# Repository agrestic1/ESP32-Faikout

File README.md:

## Support

You can support this project in many ways, including testing and diagnostics, merge requests, clearly described issues and suggestions, and [buying Faikout boards from us](https://shop.revk.uk?mrlHiG1i). Thank you all for your support. This is open source so others can make and sell (with trademark restrictions). AI based bug reports or MRs will get you blocked.

# ESP32-Faikout

Everyone knows Daikin make some of the best air conditioners out there, mechanically speaking. Sadly their WiFi control modules are not so good, especially the latest models which are all cloud based, require an internet connection to even work, and are slow.

This code/module provides local control via web interface, MQTT, and HomeAssistant integration, all with no cloud crap.

* There is also a new [Faikout Remote Control](https://remote.revk.uk/) available, BLE linked to the Faikout, with environmental sensors, available now.

I'd like to thank the contributors, but contributions are made and accepted on basis that you issue your contribution under the same GPL licence as the project. Forks are allowed on the basis that your forks are on the same GPL licence as the project.

## Trademark

This is an open source project, but bear in mind you cannot sell boards bearing the Andrews & Arnold Ltd name, the A&A logo, the registered trademark Faikout, the registered trademark AJK logo, or the GS1 allocated EANs assigned to Andrews & Arnold Ltd.

Note the name change from Faikin to Faikout as Daikin complained to Amazon and caused a lot of issues. As such Faikout is now a registered trademark to avoid such issues.

## Home Assistant Integration

There has been a lot of work on integrating with Home Assistant as a climate device, and other sensors. This is all based on using MQTT (either HA mosquitto broker, or a broker to which HA also connects). This provides real time responses and sensor data and works very well.

In addition, for other management systems than HA, the *legacy* Daikin local HTTP URLs are also supported to some extent. The support coverage is not as good, and maintence of this is less of a priority - but as always (human) suggestions and pull requests are welcome in this area. If you are using the old Daikin HA integration which uses these legacy HTTP URLs, please update to using MQTT. The config is automatic over MQTT - you just have to set the broken, username, and password. 

## Further manuals / links

- [Work in progress](https://codeberg.org/RevK/ESP32-Faikout/wiki/Work-in-progress)
- [Wiring](https://codeberg.org/RevK/ESP32-Faikout/wiki/Wiring)
- [Setup](Manuals/Setup.md) Manual
- [Controls](Manuals/Controls.md) Manual
- [Advanced](Manuals/Advanced.md) Manual
- [ESP8266 port](https://github.com/Sonic-Amiga/ESP8266-Faikin) of this code
- [list of supported air-con](https://codeberg.org/RevK/ESP32-Faikout/wiki/List-of-confirmed-working-air-con-units) WiKi (please update as needed)
- [DoC](Manuals/DoC.md) and Vulnerability disclosure policy
- [S21](Manuals/S21.md) reverse engineered details of `S21` protocol

For support, see issues.

## Safety

Always propely isolate power before opening your air-con. Take care as dangerous voltages. Some connector types have dangerous voltage in operation.

### Ethernet (and WiFi)

The Ethernet board has an RJ45 10/100 Ethernet connector for improved reliability and privacy. The Ethernet has an isolating transformer and clearances, but I have to stress **this is a prototype/dev board for specialist/hobbyist use only, and is NOT certified for grid power safety isolation. DO NOT USE WITH X403 CONNECTOR or any connector with dangerous voltages.**

### PoE Ethernet (and WiFi)

The PoE Ethernet board has an RJ45 10/100 Ethernet connector for improved reliability and privacy, with PoE power for the Faikout module. The PoE power module has electrical isolation. The board also has opto isolators for the S21 connection, electrically isolating it from the air conditioning unit. This adds extra layers of safety, however I have to stress **this is a prototype/dev board for specialist/hobbyist use only, and is NOT certified for grid power safety isolation.**

*Note that Ethernet uses more power - there are some Daikin models with much less power from the air-con, for these PoE may be a better choice for Ethernet use, as the main board (and Ethernet chip) is powered from the PoE, and not the air-con.*

## PCB and case

Buy from [shop.revk.uk](https://shop.revk.uk?mrlHiG1i). Also available from a third party in Australia eBay.

New Ethernet option.

New Opto-isiolated PoE Ethernet option.

Board are supplied in a panel, with snap off parts. The basic Faikout board can be two sizes 45x36mm or 40x16mm.

## Why I made this

The history is that, after years of using Daikin air-con in my old home, and using the local http control, in my new house in Wales the WiFi was all cloud based with no local control, and useless, and slow. Just configuring it was a nightmare. I spent all day reverse engineering it and making a new module to provide local control. Pull requests and feature ideas welcome.

This whole project is almost entirely by me, but with some valuable contributions from others (thank you). All of my bits are copyright by me and Andrews & Arnold Ltd who sponsor the whole project, and released under GPL. Whilst not required by the licence, attribution and links would be appreciated if you reuse this.

## How to get one

But also, the PCB designs are published, including production files for [JLCPCB](https://jlcpcb.com). You need to remove trademarks, etc, and you would also need something to program them (TC2030 lead). Obviously you need some experience with PCB ordering and diagnostics if getting your own boards made.

# Set-up

Appears as access point with simple web page to set up on local WiFI. On iPhone the setup page auto-loads.

# Operation

Local interactive web control page using *hostname*.local, no app required, no external internet required.

- [Setup](Manuals/Setup.md) Manual
- [Controls](Manuals/Controls.md) Manual
- [Advanced](Manuals/Advanced.md) Manual

# Design

* KiCad PCB designs included, with JLCPCB production files
* 3D printed case STL files
* Documentation of reverse engineered protocol included

Basically, Daikin have gone all cloudy with the latest WiFi controllers. This module is designed to provide an alternative.

* Simple local web based control with live websocket status, easy to save as desktop icon on a mobile phone
* MQTT reporting and controls
* Works with Home Assistant over MQTT - note Home Assistant can work with HomeKit
* Includes linux mysql/mariadb based logging and graphing tools
* Works with [EnvMon](https://codeberg.org/RevK/ESP32-EnvMon) Environmental Monitor for finer control and status display
* or, works with BlueCoinT and Telink [BLE temperature sensor](Manuals/BLE.md) as a remote reference in an auto mode
* Automatically works out if S21 or X50 protocol (used on bigger/ducted units)
* Backwards compatible direct `/aircon/...` URLs

# Building code yourself

Git clone this `--recursive` to get all the submodules, and it should build with just `make`. There are make targets for other variations, but this hardware is the `make pico` or `make s3` version. The `make` actually runs the normal `idf.py` to build which then uses cmake. `make menuconfig` can be used to fine tune the settings, but the defaults should be mostly sane. `make flash` should work to program. If flashing yourself, you will need a programming lead, e.g. [Tazmotizer](https://codeberg.org/RevK/Tasmotizer-PCB) or similar, and of course the full ESP IDF environment. The latest boards also have 4 pads for direct USB connection to flash with no adaptor. The modules on Amazon come pre-loaded and can upgrade over the air.

The code is normally set up to automatically upgrade the software, checking roughly once a week. You can change this in settings via MQTT.

If you build yourself, you either need no code signing, or your own signing key. This will break auto-updates which try to load my code releases, so you need to adjuist settings `otahost` and `otaauto` accordingly. You can set these in the build config, along with WiFi settings, etc.

## Flashing code

You will need to connect a suitable programming lead. Boards have a tag-connect compatible header for a [TC2030-USB-NL](https://www.tag-connect.com/product/tc2030-usb-nl) lead. Note that the latest boards have test pads on the back which include USB, so you can solder a USB lead if necessary.

See [https://codeberg.org/RevK/ESP32-RevK](https://codeberg.org/RevK/ESP32-RevK) for more details of how to flash the files easily.

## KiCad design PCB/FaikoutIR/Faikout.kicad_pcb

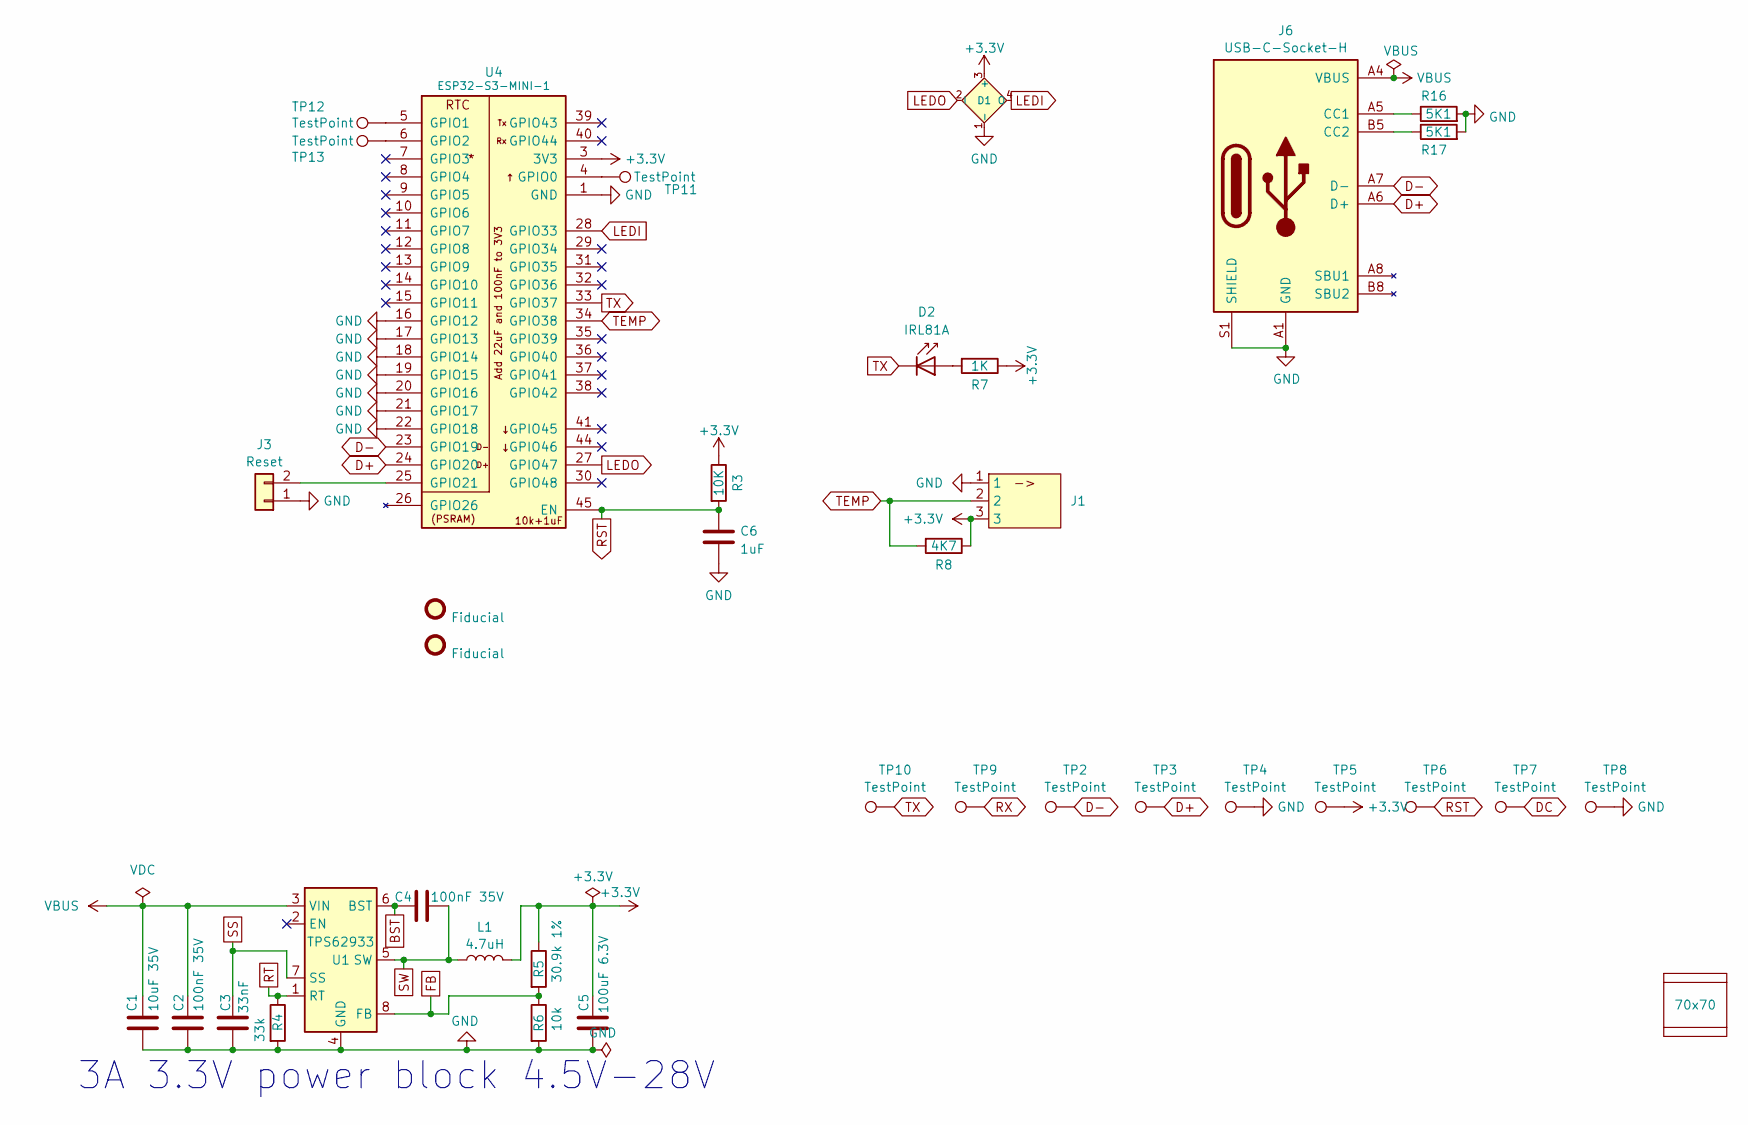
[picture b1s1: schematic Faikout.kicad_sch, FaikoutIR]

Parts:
C1: 10uF 35V; C_0603; MPN C22367827
C2, C4: 100nF 35V; C_0201; MPN C181043
C3: 33nF; C_0201; MPN C5142554
C5: 100uF 6.3V; C_0805; MPN C141660
C6: 1uF; C_0201
D1: XL-1615RGBC-2812B; SMD1615; MPN C5349954
D2: IRL81A; LED_SideEmitter_Rectangular_W4.5mm_H1.6mm
FID2, FID3: Fiducial; Fiducial_1mm_Mask2mm
J1: Wago; WAGO-2060-453-998-404; MPN C2765056
J3: Reset; AA-Pad
J6: USB-C-Socket-H; MPN C709357
L1: 4.7uH; L_6x6; MPN C32684
PCB1: 70x70; PCB7070
R3: 10K; R_0201; MPN C106225
R4: 33k; R_0201; MPN C473534
R5: 30.9k 1%; R_0201; MPN C473585
R6: 10k; R_0201; MPN C106225
R7: 1K; R_0201
R8: 4K7; R_0201
R16, R17: 5K1; R_0201; MPN C473460
TP2, TP3, TP4, TP5, TP6, TP7, TP8, TP9, TP10, TP11, TP12, TP13: TestPoint; PAD-2mm
U1: TPS62933; SOT-583-8; MPN C3200405
U4: ESP32-S3-MINI-1; MPN C3013941
V3, V4: VCUT70N

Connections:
+3.3V: C5.1, D1.3 (+), J1.3, L1.2, R3.1, R5.1, R7.1, R8.1, TP5.1 (1_1), U4.3 (3V3)
BST: C4.1, U1.6 (BST)
D+: J6.A6 (D+), J6.B6 (D+), TP3.1 (1_1), U4.24 (GPIO20)
D-: J6.A7 (D-), J6.B7 (D-), TP2.1 (1_1), U4.23 (GPIO19)
DC: TP7.1 (1_1)
FB: R5.2, R6.1, U1.8 (FB)
GND: C1.2, C2.2, C3.2, C5.2, C6.2, D1.1 (-), J1.1, J3.1, J6.A1 (GND), J6.A12 (GND), J6.B1 (GND), J6.B12 (GND), J6.S1 (SHIELD), R4.2, R6.2, R16.2, R17.2, TP4.1 (1_1), TP8.1 (1_1), U1.4 (GND), U4.1 (GND), U4.2 (GND), U4.16 (GPIO12), U4.17 (GPIO13), U4.18 (GPIO14), U4.19 (GPIO15), U4.20 (GPIO16), U4.21 (GPIO17), U4.22 (GPIO18), U4.42 (GND), U4.43 (GND), U4.46 (GND), U4.47 (GND), U4.48 (GND), U4.49 (GND), U4.50 (GND), U4.51 (GND), U4.52 (GND), U4.53 (GND), U4.54 (GND), U4.55 (GND), U4.56 (GND), U4.57 (GND), U4.58 (GND), U4.59 (GND), U4.60 (GND), U4.61 (GND), U4.62 (GND), U4.63 (GND), U4.64 (GND), U4.65 (GND)
LEDI: D1.4 (O), U4.28 (GPIO33)
LEDO: D1.2 (I), U4.27 (GPIO47)
unnamed: D2.2 (A), R7.2
unnamed: J3.2, U4.25 (GPIO21)
unnamed: J6.A5 (CC1), R16.1
unnamed: J6.B5 (CC2), R17.1
unnamed: TP11.1 (1_1), U4.4 (GPIO0)
unnamed: TP12.1 (1_1), U4.5 (GPIO1)
unnamed: TP13.1 (1_1), U4.6 (GPIO2)
RST: C6.1, R3.2, TP6.1 (1_1), U4.45 (EN)
RT: R4.1, U1.1 (RT)
RX: TP9.1 (1_1)
SS: C3.1, U1.7 (SS)
SW: C4.2, L1.1, U1.5 (SW)
TEMP: J1.2, R8.2, U4.34 (GPIO38)
TX: D2.1 (K), TP10.1 (1_1), U4.33 (GPIO37)
VBUS: C1.1, C2.1, J6.A4 (VBUS), J6.A9 (VBUS), J6.B4 (VBUS), J6.B9 (VBUS), U1.3 (VIN)

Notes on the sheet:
3A 3.3V power block 4.5V-28V

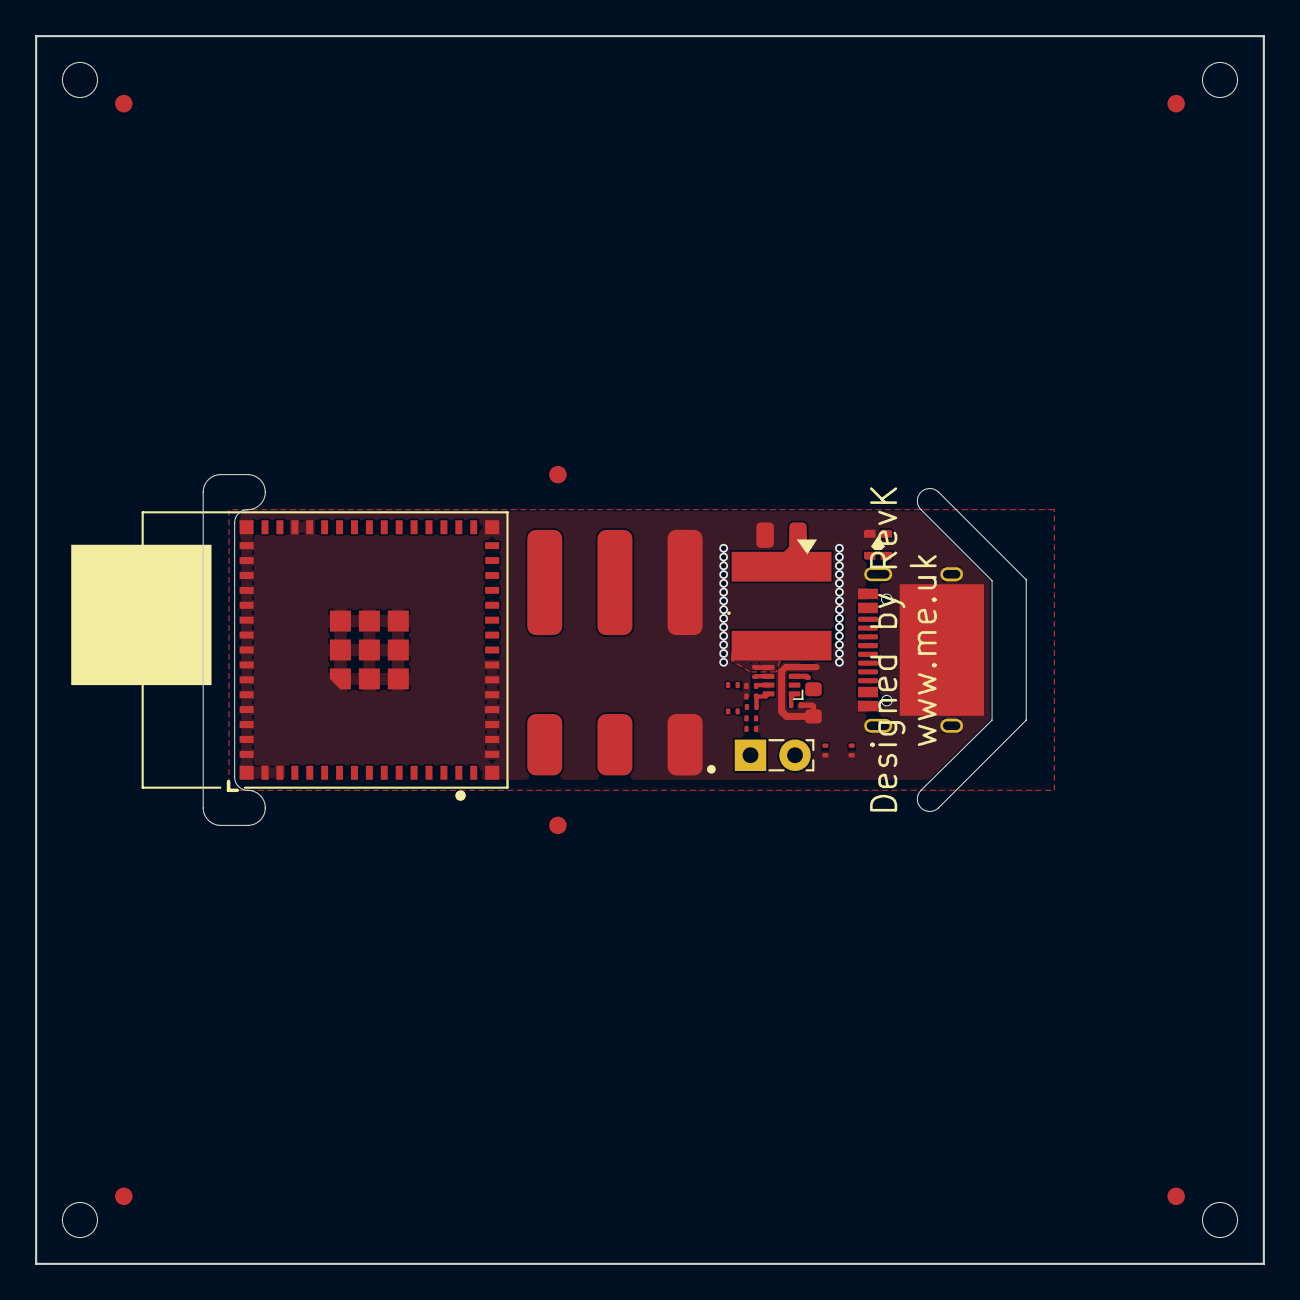
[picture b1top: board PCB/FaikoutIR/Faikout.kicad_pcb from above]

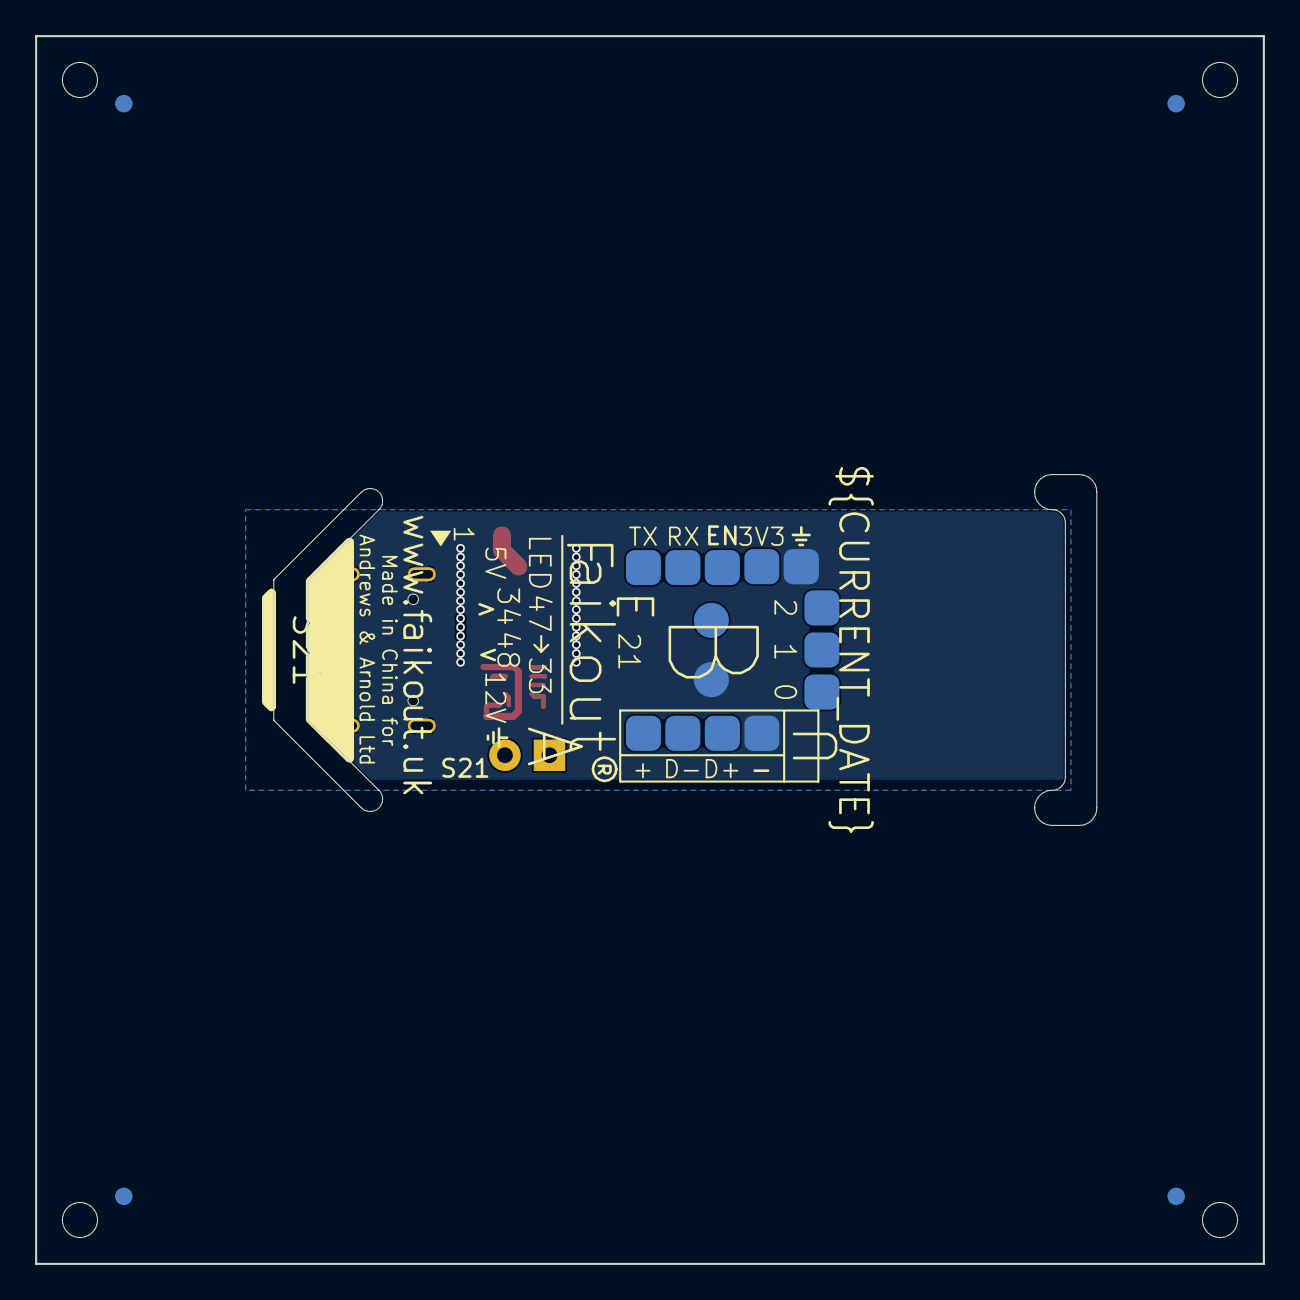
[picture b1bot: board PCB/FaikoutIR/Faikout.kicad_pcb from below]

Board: 2 copper layers, 70.0 x 70.0 mm, 39 parts (13 on the bottom side), 22 nets.

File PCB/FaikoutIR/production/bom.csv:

Designator,Footprint,Quantity,Value,LCSC Part #
C1,C_0603,1,10uF 35V,C22367827
"C2, C4",C_0201,2,100nF 35V,C181043
C3,C_0201,1,33nF,C5142554
C5,C_0805,1,100uF 6.3V,C141660
C6,C_0201,1,1uF,
D1,SMD1615,1,XL-1615RGBC-2812B,C5349954
D2,LED_SideEmitter_Rectangular_W4.5mm_H1.6mm,1,IRL81A,
J1,WAGO-2060-453-998-404,1,Wago,C2765056
J6,USB-C-Socket-H,1,USB-C-Socket-H,C709357
L1,L_6x6,1,4.7uH,C32684
"R16, R17",R_0201,2,5K1,C473460
"R3, R6",R_0201,2,10K,C106225
R4,R_0201,1,33k,C473534
R5,R_0201,1,30.9k 1%,C473585
R7,R_0201,1,1K,
R8,R_0201,1,4K7,
U1,SOT-583-8,1,TPS62933,C3200405
U4,ESP32-S3-MINI-1,1,ESP32-S3-MINI-1,C3013941

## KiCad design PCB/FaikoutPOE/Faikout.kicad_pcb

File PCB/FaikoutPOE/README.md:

# FaikoutPOE

## Trademark

This project is subject to the licence in the LICENCE file, and even if that says it is an open source project, you cannot sell boards or cases bearing the Andrews & Arnold Ltd name, the A&A logo, the registered trademark AJK logo, or other registered trademarks, or any GS1 allocated EANs/barcode assigned to Andrews & Arnold Ltd.

## PCB Designs

These files are for use with [KiCAD](https://www.kicad.org).

- [Faikout](Faikout.kicad_pro)

## 3D

3D case designs are normally automatically created from the PCB so as to ensure correct details and placement of apertures, etc.

|Design|Bottom|Top|Combined|
|------|------|---|--------|
|Faikout||||

## PCB Images Faikout

---

*Auto generated README.md 2026-10-20T12:44:44*

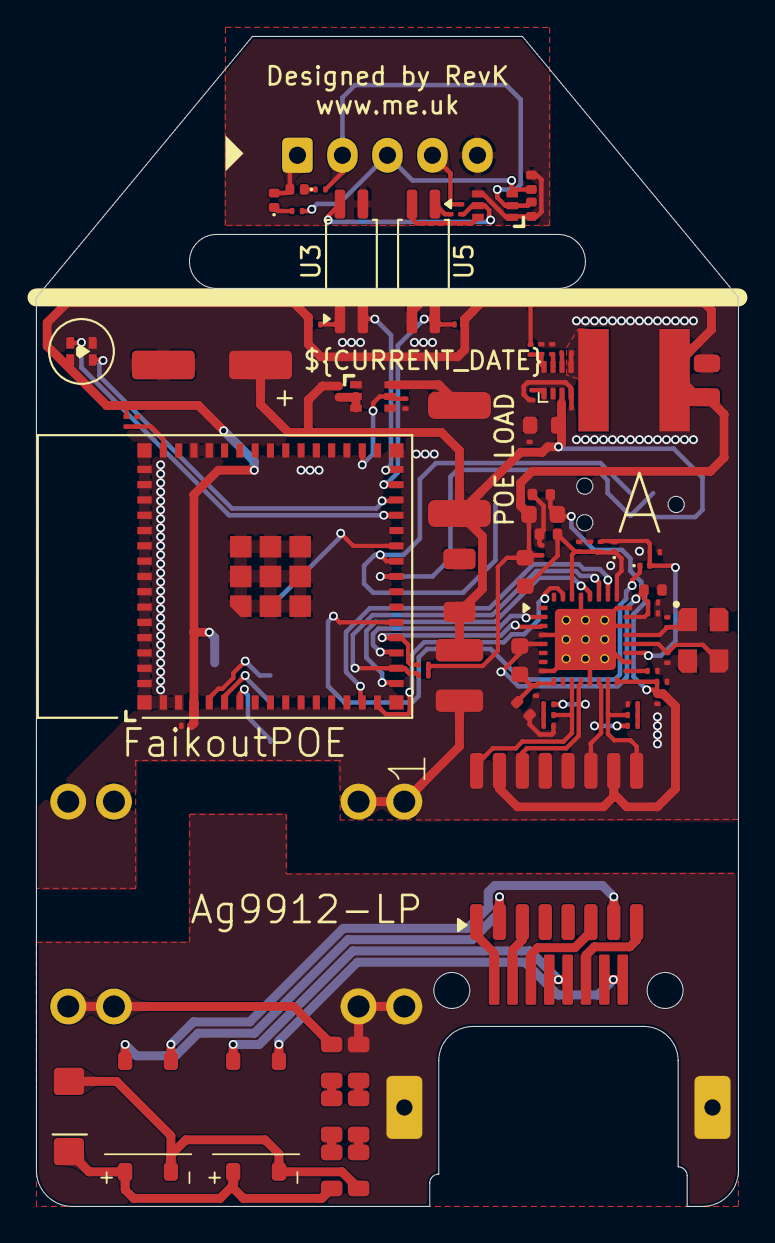
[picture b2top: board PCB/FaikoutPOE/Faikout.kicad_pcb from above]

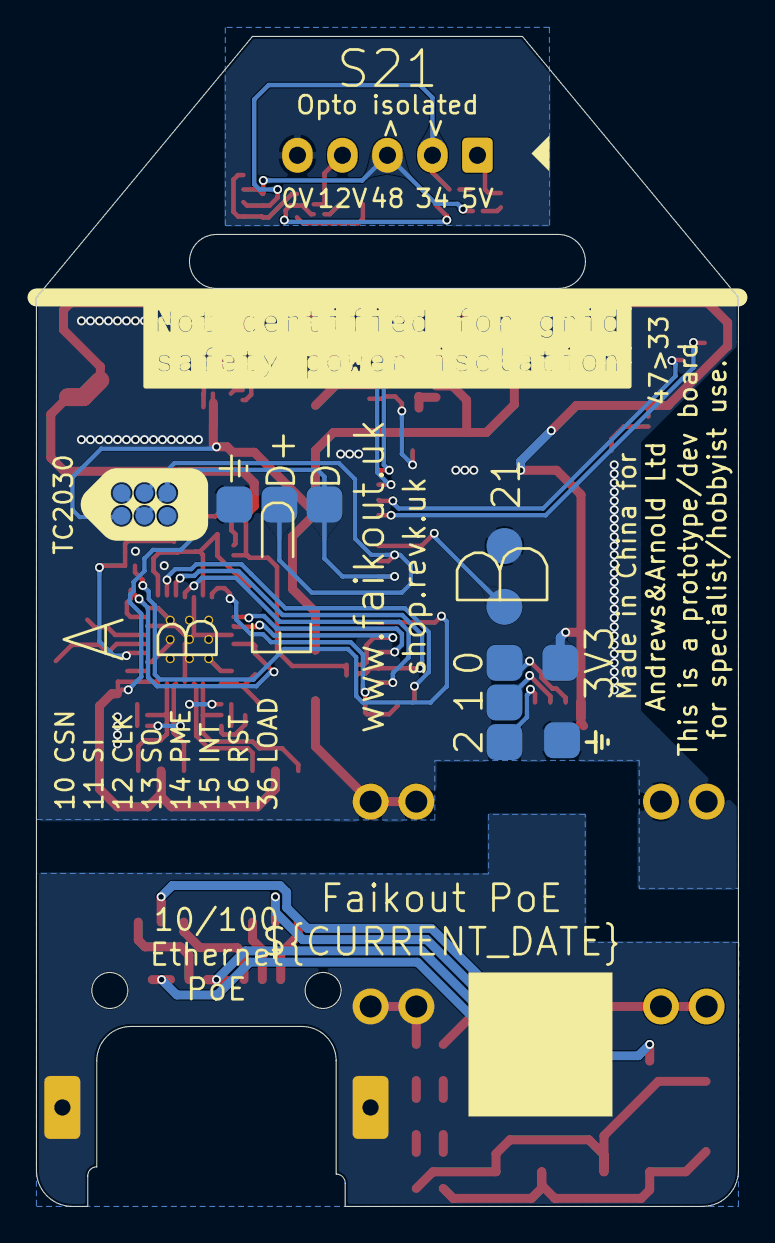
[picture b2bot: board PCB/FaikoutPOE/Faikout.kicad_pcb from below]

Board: 2 copper layers, 39.0 x 65.0 mm, 91 parts (10 on the bottom side), 71 nets.

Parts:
C1, C3, C4, C6, C8, C9, C11, C12, C13, C17, C34: 100nF; C_0201
C2, C5, C7, C10: 22uF; C_0402
C14, C15: 20pF; C_0201
C16: 10pF; C_0201
C18: 10uF 35V; C_0603
C19, C21, C22: 100nF 35V; C_0201
C20: 33nF; C_0201
C23: 100uF 6.3V; C_0805
C25: 10uF 50V; C_1206
C26: 100uF 50V; CP_Elec_6.3x7.7
C36: 1uF; C_0201
D1, D2: BAT30F4; D_0201
D4: XL-1615RGBC-2812B; SMD1615-Side
D5, D10: D; D_0402
D6: SMAJ58A; D_SMA
D7, D11: DFN1006-2L
D8, D9: MB4S; TO-269AA-BR
F4: 1210L150/33WR; Fuse_1210
FB3, FB4, FB5: FerriteBead; L_0603
J1: RJ45_LED; RC01516
J3: S21; JST_EH_S5B-EH_1x05_P2.50mm_Horizontal
J5: Reset; AA-Pad
J7: TC2030-USB-NL-DS; Tag-Connect_TC2030-IDC-NL_2x03_P1.27mm_Vertical
L1: 4.7uH; L_6x6
L14, L15, L16, L17, L18, L19: CBG201209U121T; L_0805
M1: Ag9912-LP; Ag9900-LP
P1, P2, P3, P4, P5, P6, P7, P8: Square; PAD-2mm
Q1, Q2: BSS138PS; SOT-363_SC-70-6
R1, R2, R3, R4, R5: 49R9; R_0201
R6, R7, R13, R16, R21, R22, R24: 10k; R_0201
R8: 3k01 1%; R_0201
R9: 10K; R_0201
R10, R17: 1k; R_0201
R11: 33k; R_0201
R18, R19: 4k7; R_0201
R20: 200 1W; R_2512
R23: 30.9k 1%; R_0201
TR1: B1601S
U1: KSZ8851SNL; QFN-32-1EP_5x5mm_P0.5mm_EP3.7x3.7mm-hot
U2: ESP32-S3-MINI-1
U3, U5: TCMT1100; SOP-4_4.4x2.6mm_P1.27mm
U6: TPS62933; SOT-583-8
Y1: Crystal_GND24; Crystal-3.2x2.5

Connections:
+1V8: C8.1, C9.1, C10.1, FB3.1, U1.5 (VDDCO1V8), U1.23 (VDDD1V8)
+3.3V: C17.2, C23.1, C34.2, D4.3 (+), FB4.2, FB5.2, L1.2, P7.1 (P_1), R5.1, R9.1, R17.1, R18.2, R19.2, R23.1, U2.3 (3V3)
BST: C21.1, U6.6 (BST)
CSN: U1.26 (CSN), U2.14 (GPIO10)
D+: J7.4 (D+), P3.1 (P_1), U2.24 (GPIO20)
D-: J7.2 (NC), J7.3 (D-), J7.6 (NC), P2.1 (P_1), U2.23 (GPIO19)
E12: D9.2, TR1.2 (C_TD)
E36: D9.1, TR1.7 (C_RD)
E45: D8.2, J1.4, J1.5
E78: D8.1, J1.7, J1.8
ETHRST: D1.1 (K), U2.20 (GPIO16)
FB: R23.2, R24.1, U6.8 (FB)
GND: C1.2, C2.2, C3.2, C4.2, C5.2, C6.2, C7.2, C8.2, C9.2, C10.2, C11.2, C12.2, C13.2, C14.2, C15.2, C16.2, C17.1, C18.2, C19.2, C20.2, C22.2, C23.2, C25.1, C26.2, C34.1, C36.2, D4.1 (-), J5.1, J7.5 (GND), M1.3 (-VDC), P4.1 (P_1), P8.1 (P_1), Q1.1 (SN), Q1.4 (DP), R8.1, R11.2, R22.2, R24.2, U1.4 (DGND), U1.8 (AGND), U1.13 (AGND), U1.18 (AGND), U1.22 (DGND), U1.24 (DGND), U1.29 (DGND), U1.33 (GND), U2.1 (GND), U2.2 (GND), U2.42 (GND), U2.43 (GND), U2.46 (GND), U2.47 (GND), U2.48 (GND), U2.49 (GND), U2.50 (GND), U2.51 (GND), U2.52 (GND), U2.53 (GND), U2.54 (GND), U2.55 (GND), U2.56 (GND), U2.57 (GND), U2.58 (GND), U2.59 (GND), U2.60 (GND), U2.61 (GND), U2.62 (GND), U2.63 (GND), U2.64 (GND), U2.65 (GND), U5.3, U6.4 (GND), Y1.2 (G), Y1.4 (G)
INTR: R18.1, U1.3 (INTR), U2.19 (GPIO15)
LEDI: D4.4 (O), U2.28 (GPIO33)
LEDO: D4.2 (I), U2.27 (GPIO47)
unnamed: C12.1, R1.1, R2.1
unnamed: C13.1, R3.1, R4.1
unnamed: D5.1 (K), R16.1
unnamed: D6.1 (A1), D8.3 (+), D9.3 (+), L14.1
unnamed: D6.2 (A2), D8.4 (-), D9.4 (-), L15.1
unnamed: D5.2 (A), D10.2 (A), J3.1
unnamed: D10.1 (K), R13.1
unnamed: D11.1, J3.2, Q2.2 (GN), R16.2
unnamed: D7.2, J3.3, Q2.3 (SP), R13.2
unnamed: J5.2, U2.25 (GPIO21)
unnamed: L14.2, L16.1
unnamed: L15.2, L17.1
unnamed: L16.2, L18.1
unnamed: L17.2, L19.1
unnamed: P1.1 (P_1), U2.4 (GPIO0)
unnamed: P5.1 (P_1), U2.5 (GPIO1)
unnamed: P6.1 (P_1), U2.6 (GPIO2)
unnamed: Q1.6 (DN), R20.1
unnamed: Q1.2 (GN), Q1.3 (SP), R21.2
unnamed: Q2.6 (DN), U5.2
unnamed: Q2.5 (GP), R6.2, U3.4
unnamed: R5.2, U3.1
unnamed: R10.2, U5.1
unnamed: J1.3, TR1.6 (RD+)
unnamed: J1.6, TR1.8 (RD-)
unnamed: J1.1, TR1.1 (TD+)
unnamed: J1.2, TR1.3 (TD-)
unnamed: R8.2, U1.17 (ISET)
unnamed: C6.1, C7.1, FB3.2, U1.9 (VDDA1V8)
unnamed: C15.1, U1.20 (X1), Y1.3
unnamed: C14.1, U1.21 (X2), Y1.1
unnamed: C36.1, R9.2, U2.45 (EN)
PME: U1.2 (PME), U2.18 (GPIO14)
POE: F4.2, M1.1 (+VDC), M1.2 (+VDC)
POELOAD: Q1.5 (GP), R22.1, U2.32 (GPIO36)
RSTN: C16.1, D1.2 (A), D2.2 (A), R7.2, U1.19 (RSTN)
RT: R11.1, U6.1 (RT)
RX: R17.2, U2.29 (GPIO34), U5.4
RXN: R1.2, TR1.14 (TX-), U1.12 (RXN)
RXP: R2.2, TR1.16 (TX+), U1.11 (RXP)
S21DC: J3.4, R6.1, R10.1
S21GND: D7.1, D11.2, J3.5, Q2.1 (SN), Q2.4 (DP), U3.3
SCLK: U1.28 (SCLK), U2.16 (GPIO12)
SI: U1.31 (SI), U2.15 (GPIO11)
SO: R19.1, U1.27 (SO), U2.17 (GPIO13)
SS: C20.1, U6.7 (SS)
SW: C21.2, L1.1, U6.5 (SW)
TX: U2.30 (GPIO48), U3.2
TXN: R3.2, TR1.9 (RX-), U1.15 (TXN)
TXP: R4.2, TR1.11 (RX+), U1.14 (TXP)
VDC: C18.1, C19.1, C22.1, C25.2, C26.1, F4.1, J7.1 (VBUS), R20.2, R21.1, U6.3 (VIN)
VDDA3V3: C1.1, C2.1, C11.1, FB4.1, TR1.10 (C_RX), TR1.15 (C_TX), U1.16 (VDDA3V3)
VDDIO: C3.1, C4.1, C5.1, D2.1 (K), FB5.1, R7.1, U1.25 (VDDIO), U1.30 (VDDIO)
VIN+: L18.2, M1.5 (VIN+), M1.6 (VIN+)
VIN-: J1.S, L19.2, M1.7 (VIN-), M1.8 (VIN-)

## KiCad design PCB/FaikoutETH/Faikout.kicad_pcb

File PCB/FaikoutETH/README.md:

# FaikoutETH

## Trademark

This project is subject to the licence in the LICENCE file, and even if that says it is an open source project, you cannot sell boards or cases bearing the Andrews & Arnold Ltd name, the A&A logo, the registered trademark AJK logo, or other registered trademarks, or any GS1 allocated EANs/barcode assigned to Andrews & Arnold Ltd.

## PCB Designs

These files are for use with [KiCAD](https://www.kicad.org).

- [Faikout](Faikout.kicad_pro)

## 3D

3D case designs are normally automatically created from the PCB so as to ensure correct details and placement of apertures, etc.

|Design|Bottom|Top|Combined|
|------|------|---|--------|
|Faikout||||

## PCB Images Faikout

---

*Auto generated README.md 2026-10-20T12:44:34*

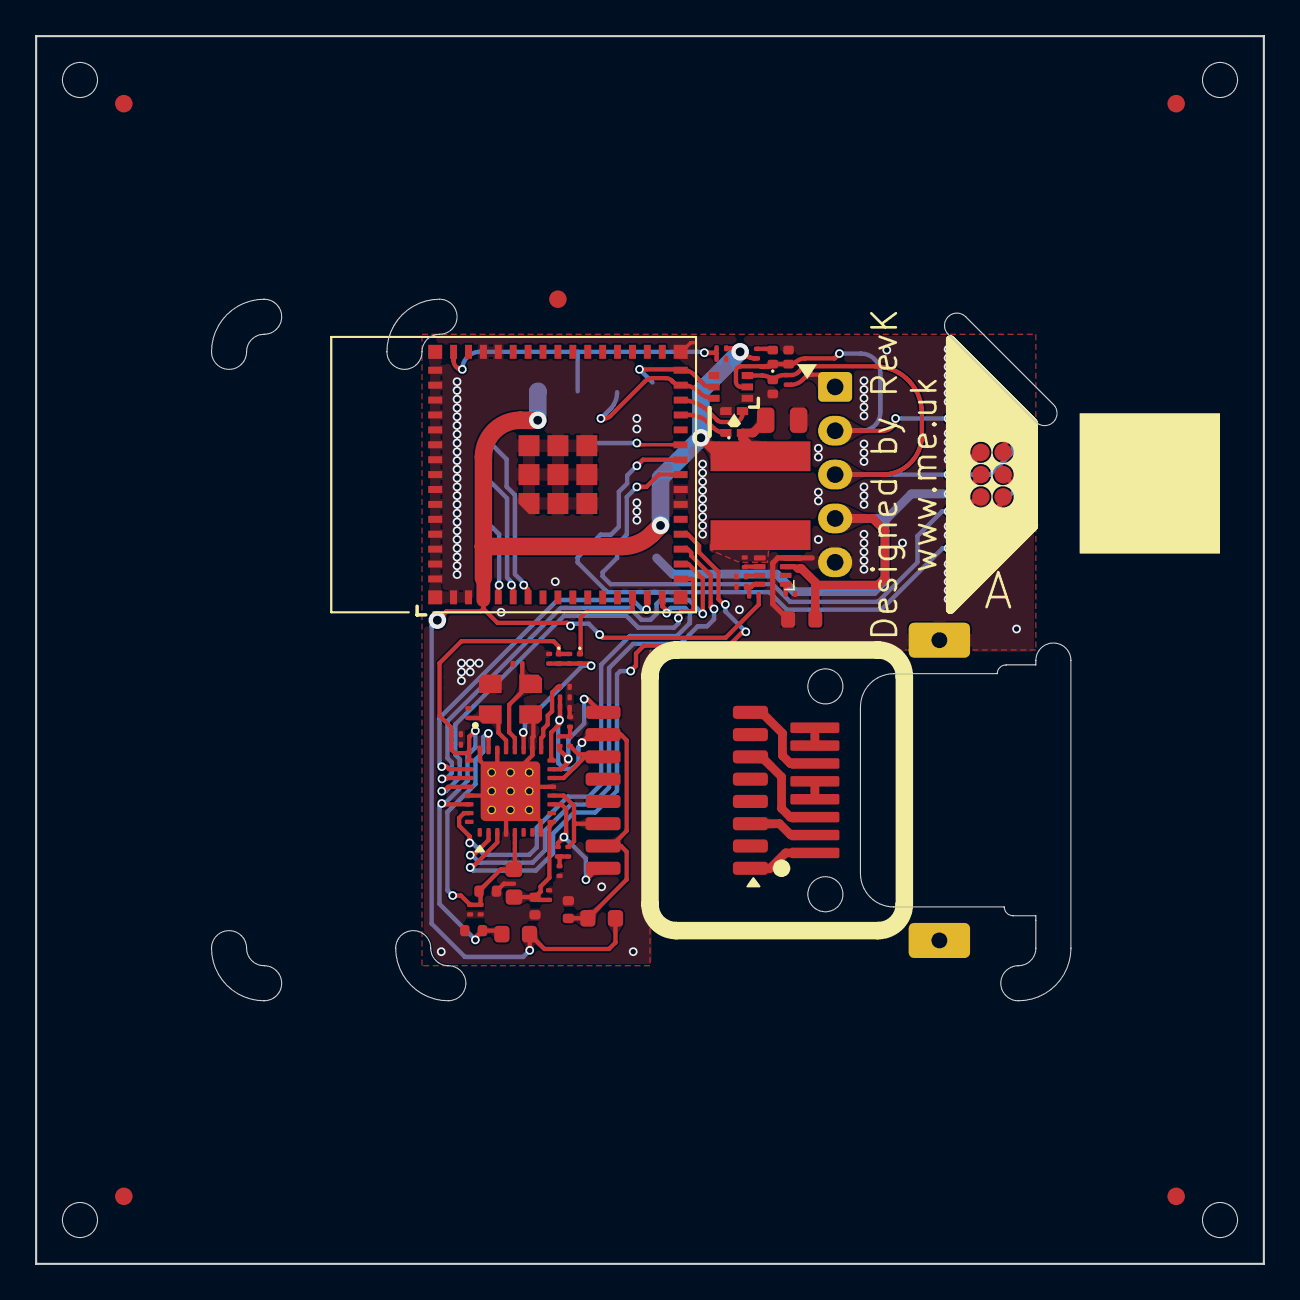
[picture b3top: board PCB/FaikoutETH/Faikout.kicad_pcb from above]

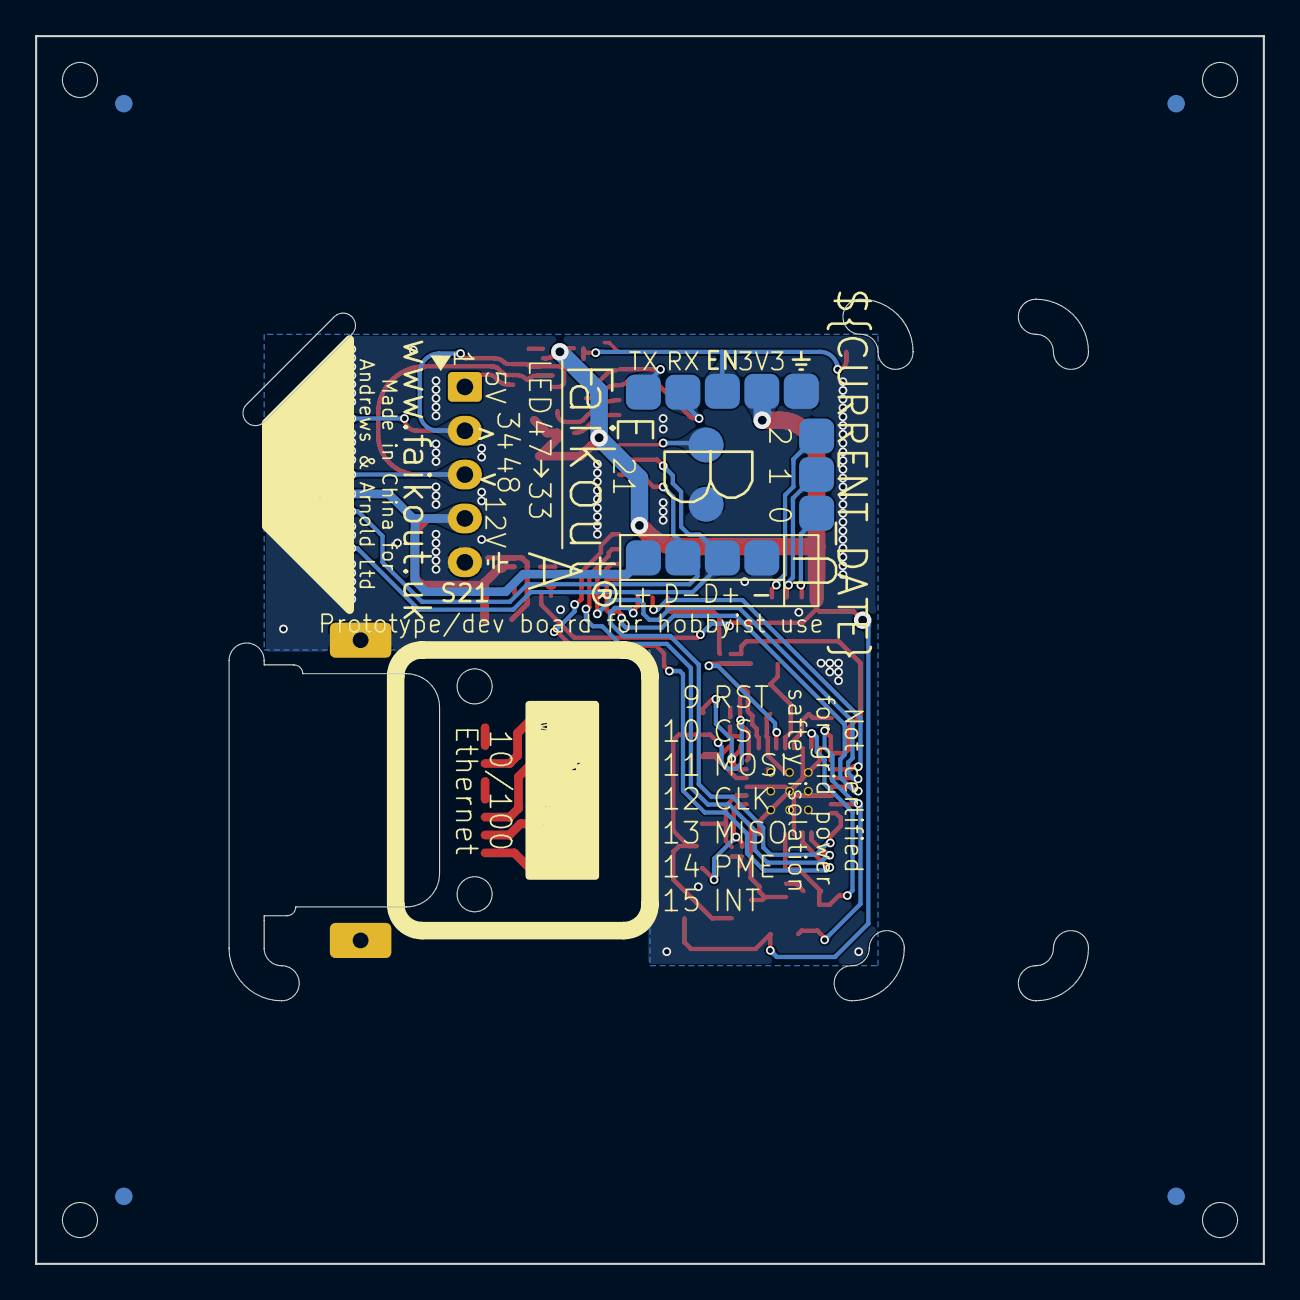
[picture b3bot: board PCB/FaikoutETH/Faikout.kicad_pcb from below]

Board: 2 copper layers, 70.0 x 70.0 mm, 73 parts (14 on the bottom side), 50 nets.

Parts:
C1: 10uF 35V; C_0603
C2, C4: 100nF 35V; C_0201
C3: 33nF; C_0201
C5: 100uF 6.3V; C_0805
C6: 1uF; C_0201
C8, C9, C11, C13, C14, C21, C22, C24, C28: 100nF; C_0201
C10, C12, C23, C25: 22uF; C_0402
C20: 10pF; C_0201
C26, C27: 20pF; C_0201
D1: XL-1615RGBC-2812B; SMD1615
D2, D3: DFN1006-2L
D4: D; D_0402
D5, D6: BAT30F4; D_0201
FB3, FB4, FB5: FerriteBead; L_0603
FID2: Fiducial; Fiducial_1mm_Mask2mm
J1: 1x5; JST_EH_S5B-EH_1x05_P2.50mm_Horizontal
J2: TC2030-USB-NL; Tag-Connect_TC2030-IDC-NL_2x03_P1.27mm_Vertical
J3: Reset; AA-Pad
J4: RJ45_LED; RC01516
L1: 4.7uH; L_6x6
PCB1: 70x70; PCB7070
Q1: BSS138PS; SOT-363_SC-70-6
R1, R2, R7, R8: 10k; R_0201
R3: 10K; R_0201
R4, R9, R10, R11: 49R9; R_0201
R5: 33k; R_0201
R6: 30.9k 1%; R_0201
R12: 3k01 1%; R_0201
TP2, TP3, TP4, TP5, TP6, TP7, TP8, TP9, TP10, TP11, TP12, TP13: TestPoint; PAD-2mm
TR1: B1601S
U1: KSZ8851SNL; QFN-32-1EP_5x5mm_P0.5mm_EP3.7x3.7mm-hot
U2: TPS62933; SOT-583-8
U4: ESP32-S3-MINI-1
V3, V4, V5, V6, V7: VCUT70N
Y1: Crystal_GND24; Crystal-3.2x2.5

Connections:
+1V8: C8.1, C9.1, C10.1, FB3.1, U1.5 (VDDCO1V8), U1.23 (VDDD1V8)
+3.3V: C5.1, D1.3 (+), FB4.2, FB5.2, L1.2, R2.1, R3.1, R6.1, TP5.1 (1_1), U4.3 (3V3)
BST: C4.1, U2.6 (BST)
CSN: U1.26 (CSN), U4.14 (GPIO10)
D+: J2.4 (D+), TP3.1 (1_1), U4.24 (GPIO20)
D-: J2.3 (D-), TP2.1 (1_1), U4.23 (GPIO19)
DC: C1.1, C2.1, J1.4, J2.1 (VBUS), TP7.1 (1_1), U2.3 (VIN)
ETHRST: D5.1 (K), U4.13 (GPIO9)
FB: R6.2, R8.1, U2.8 (FB)
GND: C1.2, C2.2, C3.2, C5.2, C6.2, C8.2, C9.2, C10.2, C11.2, C12.2, C13.2, C14.2, C20.2, C21.2, C22.2, C23.2, C24.2, C25.2, C26.2, C27.2, C28.2, D1.1 (-), D2.1, D3.1, J1.5, J2.5 (GND), J3.1, J4.S, Q1.1 (SN), Q1.4 (DP), R5.2, R8.2, R12.1, TP4.1 (1_1), TP8.1 (1_1), U1.4 (DGND), U1.8 (AGND), U1.13 (AGND), U1.18 (AGND), U1.22 (DGND), U1.24 (DGND), U1.29 (DGND), U1.33 (GND), U2.4 (GND), U4.1 (GND), U4.2 (GND), U4.21 (GPIO17), U4.22 (GPIO18), U4.42 (GND), U4.43 (GND), U4.46 (GND), U4.47 (GND), U4.48 (GND), U4.49 (GND), U4.50 (GND), U4.51 (GND), U4.52 (GND), U4.53 (GND), U4.54 (GND), U4.55 (GND), U4.56 (GND), U4.57 (GND), U4.58 (GND), U4.59 (GND), U4.60 (GND), U4.61 (GND), U4.62 (GND), U4.63 (GND), U4.64 (GND), U4.65 (GND), Y1.2 (G), Y1.4 (G)
INTR: U1.3 (INTR), U4.19 (GPIO15)
LEDI: D1.4 (O), U4.28 (GPIO33)
LEDO: D1.2 (I), U4.27 (GPIO47)
unnamed: C13.1, R4.1, R9.1
unnamed: C14.1, R10.1, R11.1
unnamed: D4.2 (A), R2.2
unnamed: D3.2, D4.1 (K), J1.2, J2.6, Q1.2 (GN)
unnamed: J1.1, R1.1
unnamed: D2.2, J1.3, J2.2, Q1.3 (SP), R1.2
unnamed: J3.2, U4.25 (GPIO21)
unnamed: J4.3, TR1.6 (RD+)
unnamed: J4.6, TR1.8 (RD-)
unnamed: J4.1, TR1.1 (TD+)
unnamed: J4.2, TR1.3 (TD-)
unnamed: R12.2, U1.17 (ISET)
unnamed: C11.1, C12.1, FB3.2, U1.9 (VDDA1V8)
unnamed: C27.1, U1.20 (X1), Y1.3
unnamed: C26.1, U1.21 (X2), Y1.1
unnamed: TP13.1 (1_1), U4.4 (GPIO0)
unnamed: TP11.1 (1_1), U4.5 (GPIO1)
unnamed: TP12.1 (1_1), U4.6 (GPIO2)
PME: U1.2 (PME), U4.18 (GPIO14)
RST: C6.1, R3.2, TP6.1 (1_1), U4.45 (EN)
RSTN: C20.1, D5.2 (A), D6.2 (A), R7.2, U1.19 (RSTN)
RT: R5.1, U2.1 (RT)
RX: Q1.6 (DN), TP9.1 (1_1), U4.29 (GPIO34)
RXN: R4.2, TR1.14 (TX-), U1.12 (RXN)
RXP: R9.2, TR1.16 (TX+), U1.11 (RXP)
SCLK: U1.28 (SCLK), U4.16 (GPIO12)
SI: U1.31 (SI), U4.15 (GPIO11)
SO: U1.27 (SO), U4.17 (GPIO13)
SS: C3.1, U2.7 (SS)
SW: C4.2, L1.1, U2.5 (SW)
TX: Q1.5 (GP), TP10.1 (1_1), U4.30 (GPIO48)
TXN: R10.2, TR1.9 (RX-), U1.15 (TXN)
TXP: R11.2, TR1.11 (RX+), U1.14 (TXP)
VB1: J4.4, J4.5
VB2: J4.7, J4.8
VDDA3V3: C24.1, C25.1, C28.1, FB4.1, TR1.10 (C_RX), TR1.15 (C_TX), U1.16 (VDDA3V3)
VDDIO: C21.1, C22.1, C23.1, D6.1 (K), FB5.1, R7.1, U1.25 (VDDIO), U1.30 (VDDIO)
